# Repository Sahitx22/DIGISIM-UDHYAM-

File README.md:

# DIGISIM-UDYAM-
Digisim implementation

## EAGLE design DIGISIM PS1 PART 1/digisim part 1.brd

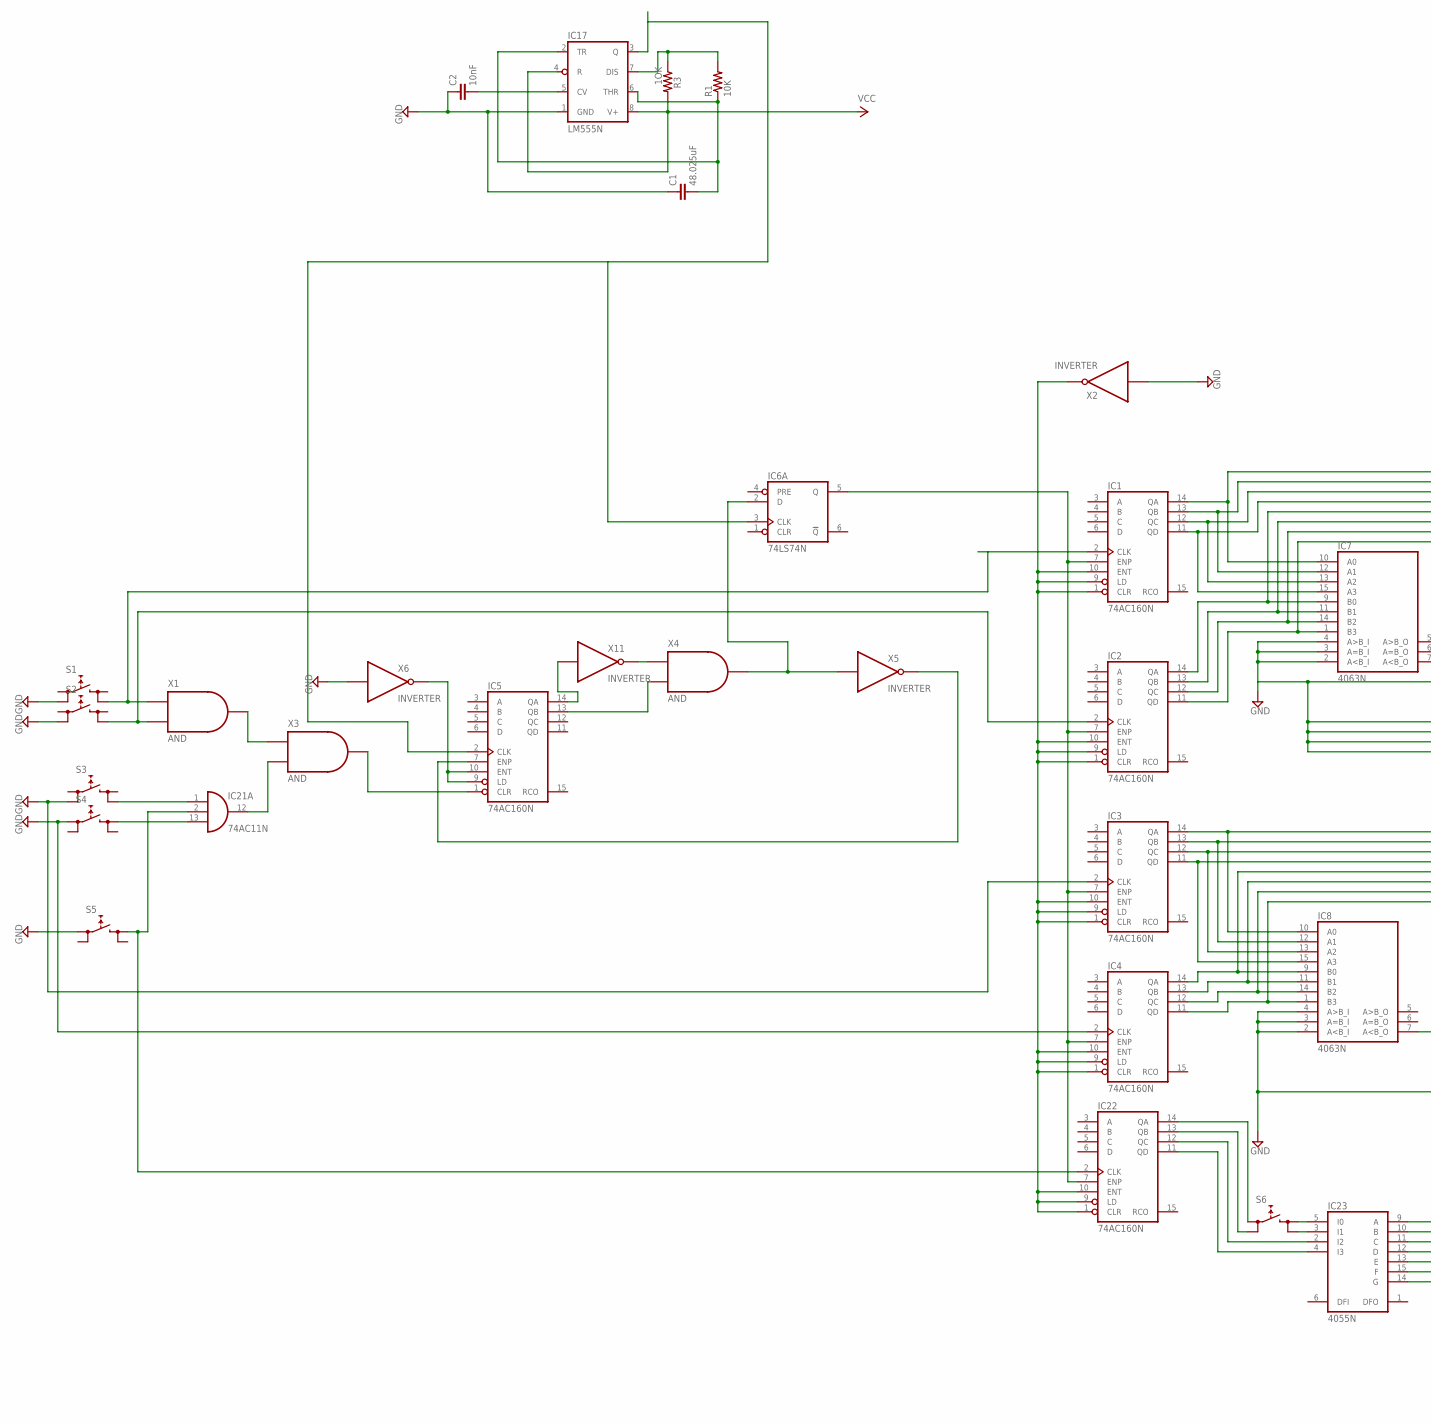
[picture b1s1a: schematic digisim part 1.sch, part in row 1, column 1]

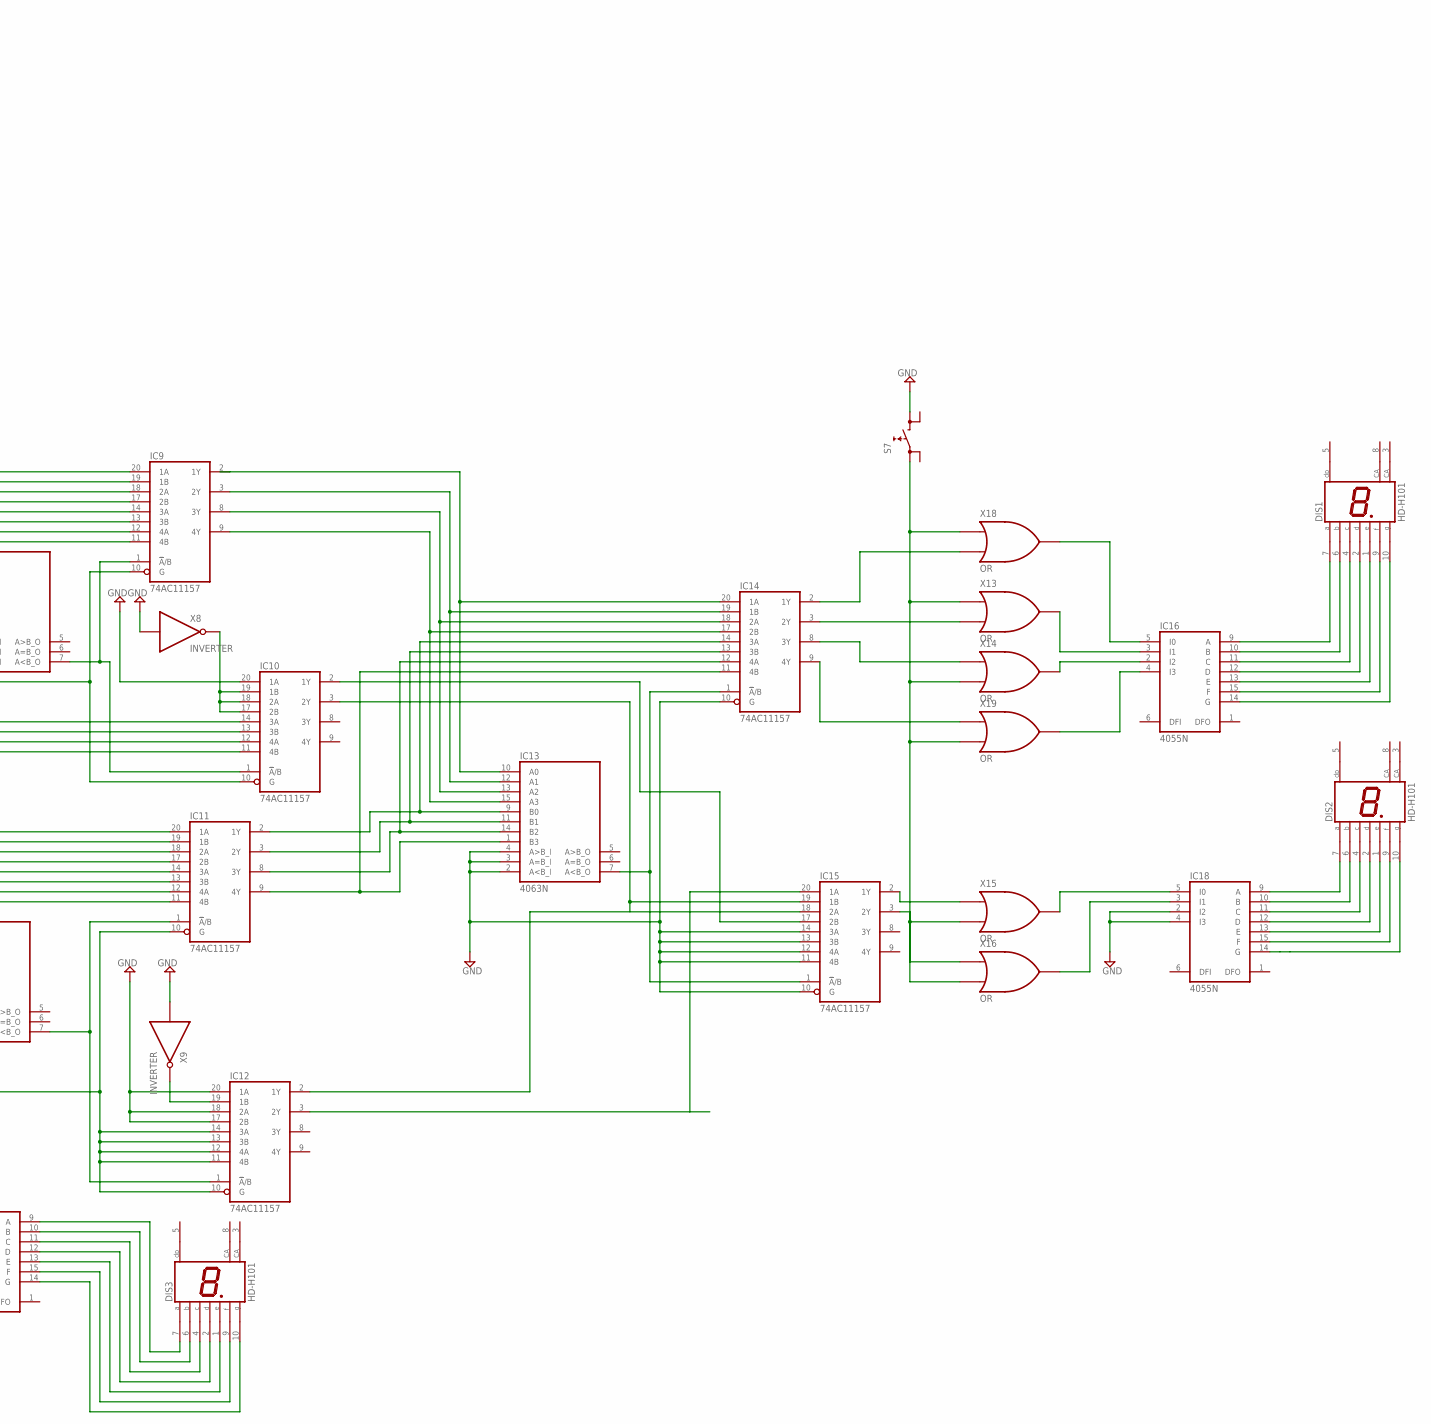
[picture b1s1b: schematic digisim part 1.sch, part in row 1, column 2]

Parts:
C1: 48.025uF; C2.5-2
C2: 10nF; C2.5-2
DIS1, DIS2, DIS3: HD-H101; HDSP-M
IC1, IC2, IC3, IC4, IC5, IC22: 74AC160N; DIL16
IC6: 74LS74N; DIL14
IC7, IC8, IC13: 4063N; DIL16
IC9, IC10, IC11, IC12, IC14, IC15: 74AC11157; DIL20
IC16, IC18, IC23: 4055N; DIL16
IC17: LM555N; DIL08
IC21: 74AC11N; DIL14
R1: 10K; 0204/5
R3: 1OK; 0204V
S1, S2, S3, S4, S5, S6, S7: REKN

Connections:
GND: C1.1, C2.1, IC1.8 (GND), IC2.8 (GND), IC3.2 (CLK), IC3.8 (GND), IC4.2 (CLK), IC4.8 (GND), IC5.8 (GND), IC6.7 (GND), IC7.2 (A<B_I), IC7.3 (A=B_I), IC7.4 (A>B_I), IC8.2 (A<B_I), IC8.3 (A=B_I), IC8.4 (A>B_I), IC9.4 (GND), IC9.5 (GND), IC9.6 (GND), IC9.7 (GND), IC9.10 (G), IC10.4 (GND), IC10.5 (GND), IC10.6 (GND), IC10.7 (GND), IC10.10 (G), IC10.11 (4B), IC10.12 (4A), IC10.13 (3B), IC10.14 (3A), IC10.20 (1A), IC11.4 (GND), IC11.5 (GND), IC11.6 (GND), IC11.7 (GND), IC11.10 (G), IC12.4 (GND), IC12.5 (GND), IC12.6 (GND), IC12.7 (GND), IC12.10 (G), IC12.11 (4B), IC12.12 (4A), IC12.13 (3B), IC12.14 (3A), IC12.17 (2B), IC12.18 (2A), IC12.20 (1A), IC13.2 (A<B_I), IC13.3 (A=B_I), IC13.4 (A>B_I), IC14.4 (GND), IC14.5 (GND), IC14.6 (GND), IC14.7 (GND), IC14.10 (G), IC15.4 (GND), IC15.5 (GND), IC15.6 (GND), IC15.7 (GND), IC15.10 (G), IC15.11 (4B), IC15.12 (4A), IC15.13 (3B), IC15.14 (3A), IC16.8 (GND), IC17.1 (GND), IC18.2 (I2), IC18.4 (I3), IC18.8 (GND), IC21.7 (GND), IC22.8 (GND), IC23.8 (GND), S1.0B (0), S2.0B (0), S3.0B (0), S4.0A (0), S5.0A (0), S7.1A (1)
unnamed: IC22.14 (QA), S6.0A (0)
unnamed: IC5.9 (LD), IC5.10 (ENT)
unnamed: IC1.1 (CLR), IC1.9 (LD), IC1.10 (ENT), IC2.1 (CLR), IC2.9 (LD), IC2.10 (ENT), IC3.1 (CLR), IC3.9 (LD), IC3.10 (ENT), IC4.1 (CLR), IC4.9 (LD), IC4.10 (ENT), IC22.1 (CLR), IC22.9 (LD), IC22.10 (ENT)
unnamed: IC1.2 (CLK), S1.1B (1)
unnamed: IC2.2 (CLK), S2.1B (1)
unnamed: IC21.1 (I0), S3.1B (1)
unnamed: IC21.13 (I2), S4.1A (1)
unnamed: IC1.14 (QA), IC7.10 (A0), IC9.20 (1A)
unnamed: IC1.13 (QB), IC7.12 (A1), IC9.19 (1B)
unnamed: IC1.12 (QC), IC7.13 (A2), IC9.18 (2A)
unnamed: IC1.11 (QD), IC7.15 (A3), IC9.17 (2B)
unnamed: IC2.14 (QA), IC7.9 (B0), IC9.14 (3A)
unnamed: IC2.13 (QB), IC7.11 (B1), IC9.13 (3B)
unnamed: IC2.12 (QC), IC7.14 (B2), IC9.12 (4A)
unnamed: IC2.11 (QD), IC7.1 (B3), IC9.11 (4B)
unnamed: IC7.7 (A<B_O), IC9.1 (!A!/B), IC10.1 (!A!/B)
unnamed: IC3.14 (QA), IC8.10 (A0), IC11.20 (1A)
unnamed: IC3.13 (QB), IC8.12 (A1), IC11.19 (1B)
unnamed: IC3.12 (QC), IC8.13 (A2), IC11.18 (2A)
unnamed: IC3.11 (QD), IC8.15 (A3), IC11.17 (2B)
unnamed: IC4.14 (QA), IC8.9 (B0), IC11.14 (3A)
unnamed: IC4.13 (QB), IC8.11 (B1), IC11.13 (3B)
unnamed: IC4.12 (QC), IC8.14 (B2), IC11.12 (4A)
unnamed: IC4.11 (QD), IC8.1 (B3), IC11.11 (4B)
unnamed: IC10.17 (2B), IC10.18 (2A), IC10.19 (1B)
unnamed: IC8.7 (A<B_O), IC11.1 (!A!/B), IC12.1 (!A!/B)
unnamed: IC9.2 (1Y), IC13.10 (A0), IC14.20 (1A)
unnamed: IC9.3 (2Y), IC13.12 (A1), IC14.19 (1B)
unnamed: IC9.8 (3Y), IC13.13 (A2), IC14.18 (2A)
unnamed: IC9.9 (4Y), IC13.15 (A3), IC14.17 (2B)
unnamed: IC11.2 (1Y), IC13.9 (B0), IC14.14 (3A)
unnamed: IC11.3 (2Y), IC13.11 (B1), IC14.13 (3B)
unnamed: IC1.7 (ENP), IC2.7 (ENP), IC3.7 (ENP), IC4.7 (ENP), IC6.5 (Q), IC22.7 (ENP)
unnamed: IC12.2 (1Y), IC15.18 (2A)
unnamed: IC13.7 (A<B_O), IC14.1 (!A!/B), IC15.1 (!A!/B)
unnamed: IC10.2 (1Y), IC15.17 (2B)
unnamed: IC10.3 (2Y), IC15.19 (1B)
unnamed: IC12.3 (2Y), IC15.20 (1A)
unnamed: DIS1.7 (A), IC16.9 (A)
unnamed: DIS1.6 (B), IC16.10 (B)
unnamed: DIS1.4 (C), IC16.11 (C)
unnamed: DIS1.2 (D), IC16.12 (D)
unnamed: DIS1.1 (E), IC16.13 (E)
unnamed: DIS1.9 (F), IC16.15 (F)
unnamed: DIS1.10 (G), IC16.14 (G)
unnamed: DIS2.7 (A), IC18.9 (A)
unnamed: DIS2.6 (B), IC18.10 (B)
unnamed: IC11.9 (4Y), IC13.1 (B3), IC14.11 (4B)
unnamed: IC11.8 (3Y), IC13.14 (B2), IC14.12 (4A)
unnamed: IC21.2 (I1), IC22.2 (CLK), S5.1A (1)
unnamed: IC22.13 (QB), S6.0B (0)
unnamed: IC22.12 (QC), IC23.2 (I2)
unnamed: IC22.11 (QD), IC23.4 (I3)
unnamed: DIS3.7 (A), IC23.9 (A)
unnamed: DIS3.6 (B), IC23.10 (B)
unnamed: DIS3.4 (C), IC23.11 (C)
unnamed: DIS3.2 (D), IC23.12 (D)
unnamed: DIS3.1 (E), IC23.13 (E)
unnamed: DIS3.9 (F), IC23.15 (F)
unnamed: DIS3.10 (G), IC23.14 (G)
unnamed: IC23.3 (I1), S6.1B (1)
unnamed: IC23.5 (I0), S6.1A (1)
unnamed: DIS2.4 (C), IC18.11 (C)
unnamed: DIS2.2 (D), IC18.12 (D)
unnamed: DIS2.1 (E), IC18.13 (E)
unnamed: DIS2.9 (F), IC18.15 (F)
unnamed: DIS2.10 (G), IC18.14 (G)
unnamed: C2.2, IC17.5 (CV)
unnamed: IC17.7 (DIS), R1.2, R3.1
unnamed: C1.2, IC17.2 (TR), IC17.6 (THR), R1.1
unnamed: IC5.2 (CLK), IC6.3 (CLK), IC17.3 (Q)
VCC: IC1.16 (VCC), IC2.16 (VCC), IC3.16 (VCC), IC4.16 (VCC), IC5.16 (VCC), IC6.14 (VCC), IC9.15 (VCC), IC9.16 (VCC), IC10.15 (VCC), IC10.16 (VCC), IC11.15 (VCC), IC11.16 (VCC), IC12.15 (VCC), IC12.16 (VCC), IC14.15 (VCC), IC14.16 (VCC), IC15.15 (VCC), IC15.16 (VCC), IC16.16 (VCC), IC17.4 (R), IC17.8 (V+), IC18.16 (VCC), IC21.14 (VCC), IC22.16 (VCC), IC23.16 (VCC), R3.2
VDD: IC7.16 (VDD), IC8.16 (VDD), IC13.16 (VDD)
VEE: IC16.7 (VEE), IC18.7 (VEE), IC23.7 (VEE)
VSS: IC7.8 (VSS), IC8.8 (VSS), IC13.8 (VSS)

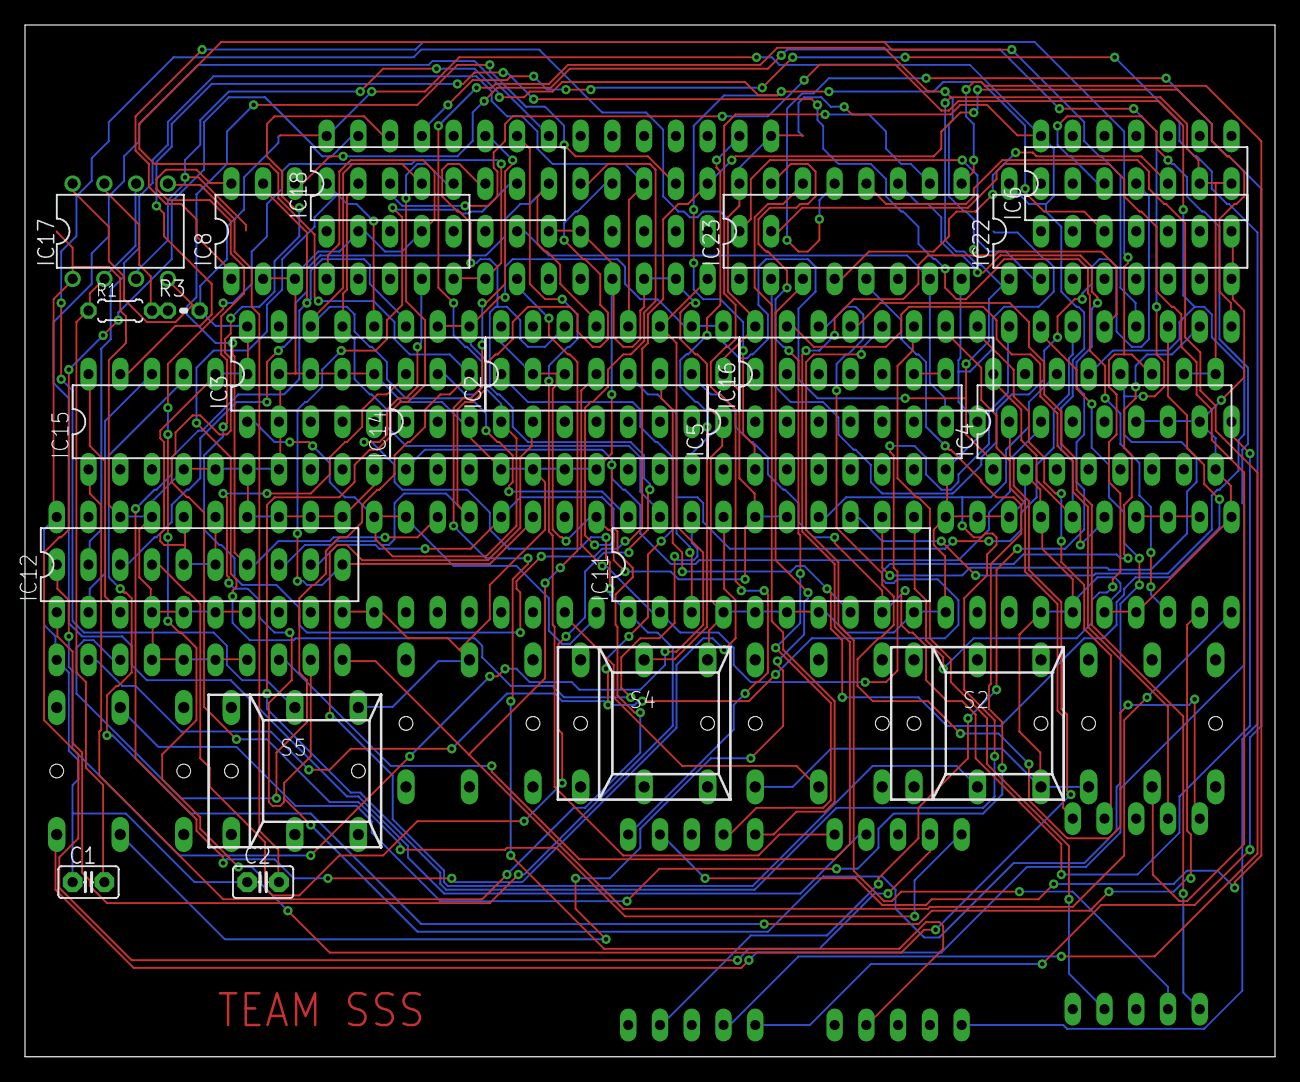
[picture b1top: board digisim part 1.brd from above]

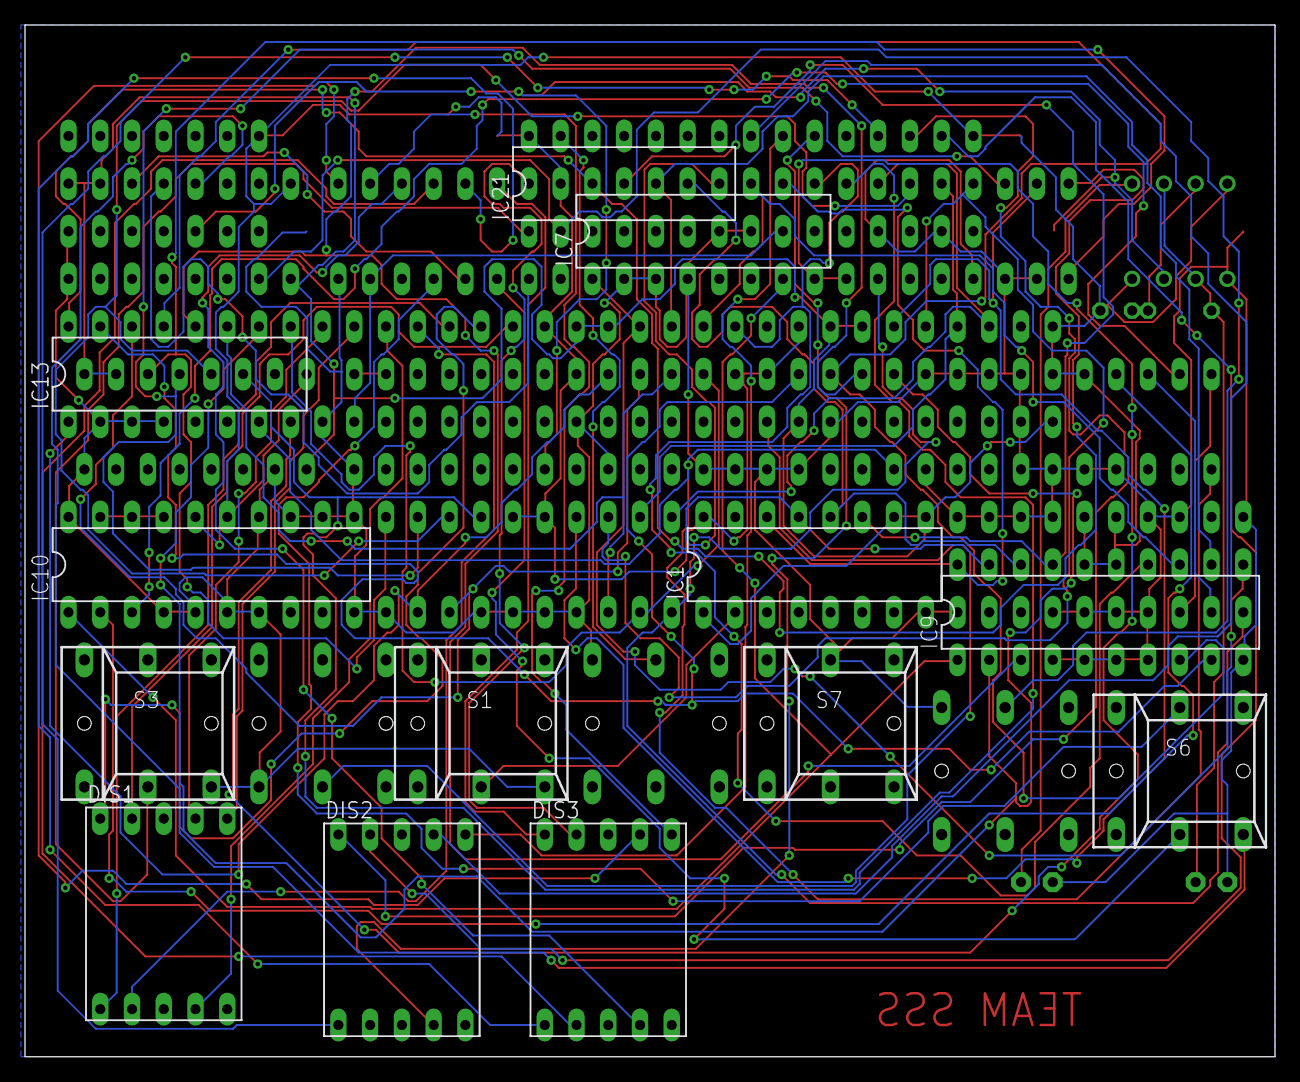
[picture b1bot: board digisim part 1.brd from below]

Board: 2 copper layers, 100.0 x 82.5 mm, 35 parts (13 on the bottom side), 76 nets.

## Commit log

2024-06-17 Create Digisim ps1
